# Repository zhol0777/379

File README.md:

# 379

this is a pcb replacement for the noxary 378. pinout isn't the same.

pcb edge cuts were provided by islandworks studio.

thanks to invis and chippy for providing plate file, xondat discord is shut down so you can't get in no more.

thanks to xyz for simple stm boot circuit.

untested. good luck.

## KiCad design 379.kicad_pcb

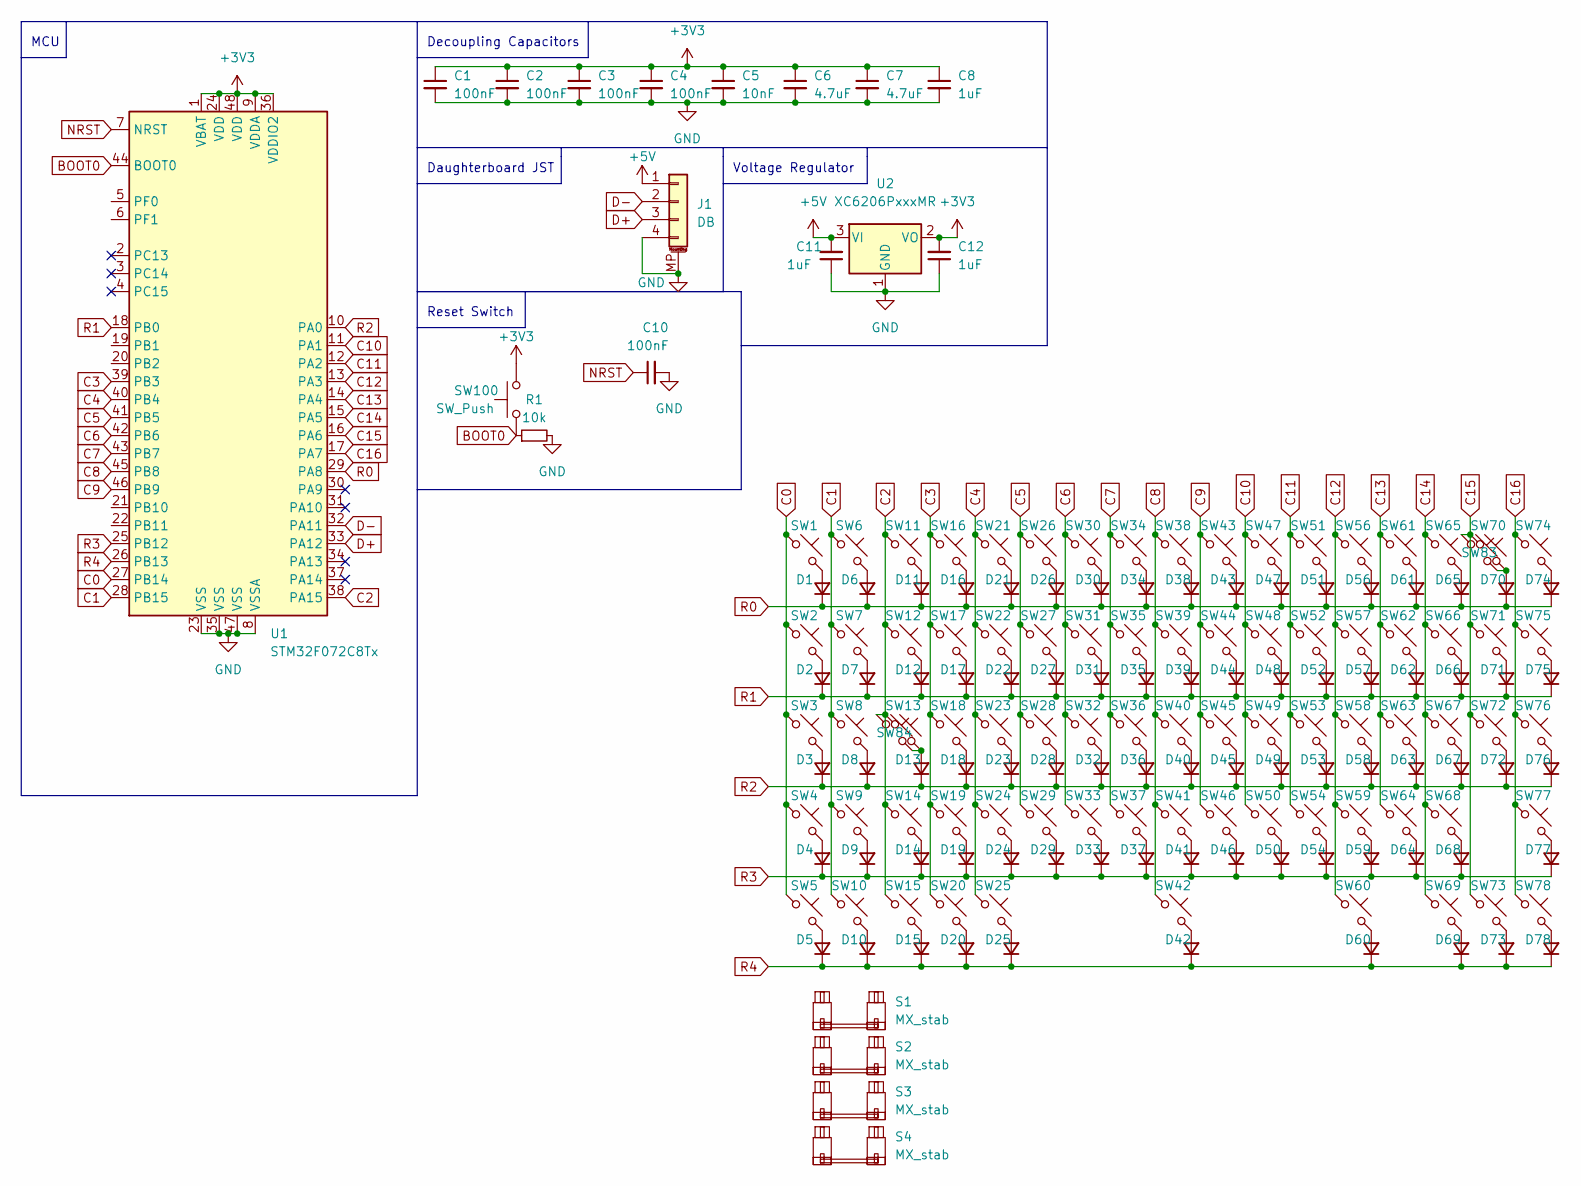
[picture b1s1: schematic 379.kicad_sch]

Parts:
C1, C2, C3, C4, C10: 100nF; C_0402_1005Metric
C5: 10nF; C_0402_1005Metric
C6, C7: 4.7uF; C_0402_1005Metric
C8, C11, C12: 1uF; C_0402_1005Metric
D1, D2, D3, D4, D5, D6, D7, D8, D9, D10, D11, D12, D13, D14, D15, D16, D17, D18, D19, D20, D21, D22, D23, D24, D25, D26, D27, D28, D29, D30, D31, D32, D33, D34, D35, D36, D37, D38, D39, D40, D41, D42, D43, D44, D45, D46, D47, D48, D49, D50, D51, D52, D53, D54, D56, D57, D58, D59, D60, D61, D62, D63, D64, D65, D66, D67, D68, D69, D70, D71, D72, D73, D74, D75, D76, D77, D78: D_Small; D_SOD-123
J1: DB; JST_SH_SM04B-SRSS-TB_1x04-1MP_P1.00mm_Horizontal
R1: 10k; R_0603_1608Metric
S1: MX_stab; STAB_MX_P_2u
S2, S3: MX_stab; STAB_MX_2.25u
S4: MX_stab; STAB_MX_7u
SW1, SW2, SW3, SW4, SW5, SW6, SW7, SW8, SW9, SW10, SW11, SW14, SW16, SW17, SW18, SW19, SW20, SW21, SW22, SW23, SW24, SW26, SW27, SW28, SW29, SW30, SW31, SW32, SW33, SW34, SW35, SW36, SW37, SW38, SW39, SW40, SW41, SW42, SW43, SW44, SW45, SW46, SW47, SW48, SW49, SW50, SW51, SW52, SW53, SW54, SW56, SW57, SW58, SW59, SW61, SW62, SW63, SW64, SW65, SW66, SW67, SW68, SW69, SW70, SW71, SW72, SW73, SW74, SW75, SW76, SW77, SW78, SW83: MX_SW_solder; SW_MX_1u
SW12, SW15, SW25, SW60: MX_SW_solder; SW_MX_1.5u
SW13: MX_SW_solder; SW_MX_1.75u
SW84: MX_SW_solder; SW_MX_1.75u_STP_1.25
SW100: SW_Push; PinHeader_1x02_P2.00mm_Vertical
U1: STM32F072C8Tx; LQFP-48_7x7mm_P0.5mm
U2: XC6206PxxxMR; SOT-23

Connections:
+3V3: C1.1, C2.1, C3.1, C4.1, C5.1, C6.1, C7.1, C8.1, C12.2, SW100.2, U1.1 (VBAT), U1.9 (VDDA), U1.24 (VDD), U1.36 (VDDIO2), U1.48 (VDD), U2.2 (VO)
+5V: C11.2, J1.1, U2.3 (VI)
BOOT0: R1.1, SW100.1, U1.44 (BOOT0)
C0: SW1.1, SW2.1, SW3.1, SW4.1, SW5.1, U1.27 (PB14)
C1: SW6.1, SW7.1, SW8.1, SW9.1, SW10.1, U1.28 (PB15)
C2: SW11.1, SW12.1, SW13.1, SW14.1, SW15.1, SW84.1, U1.38 (PA15)
C3: SW16.1, SW17.1, SW18.1, SW19.1, SW20.1, U1.39 (PB3)
C4: SW21.1, SW22.1, SW23.1, SW24.1, SW25.1, U1.40 (PB4)
C5: SW26.1, SW27.1, SW28.1, SW29.1, U1.41 (PB5)
C6: SW30.1, SW31.1, SW32.1, SW33.1, U1.42 (PB6)
C7: SW34.1, SW35.1, SW36.1, SW37.1, U1.43 (PB7)
C8: SW38.1, SW39.1, SW40.1, SW41.1, SW42.1, U1.45 (PB8)
C9: SW43.1, SW44.1, SW45.1, SW46.1, U1.46 (PB9)
C10: SW47.1, SW48.1, SW49.1, SW50.1, U1.11 (PA1)
C11: SW51.1, SW52.1, SW53.1, SW54.1, U1.12 (PA2)
C12: SW56.1, SW57.1, SW58.1, SW59.1, SW60.1, U1.13 (PA3)
C13: SW61.1, SW62.1, SW63.1, SW64.1, U1.14 (PA4)
C14: SW65.1, SW66.1, SW67.1, SW68.1, SW69.1, U1.15 (PA5)
C15: SW70.1, SW71.1, SW72.1, SW73.1, SW83.1, U1.16 (PA6)
C16: SW74.1, SW75.1, SW76.1, SW77.1, SW78.1, U1.17 (PA7)
D+: J1.3, U1.33 (PA12)
D-: J1.2, U1.32 (PA11)
GND: C1.2, C2.2, C3.2, C4.2, C5.2, C6.2, C7.2, C8.2, C10.2, C11.1, C12.1, J1.4, J1.MP (MountPin), R1.2, U1.8 (VSSA), U1.23 (VSS), U1.35 (VSS), U1.47 (VSS), U2.1 (GND)
NRST: C10.1, U1.7 (NRST)
unnamed: D1.2 (A), SW1.2
unnamed: D2.2 (A), SW2.2
unnamed: D3.2 (A), SW3.2
unnamed: D4.2 (A), SW4.2
unnamed: D5.2 (A), SW5.2
unnamed: D6.2 (A), SW6.2
unnamed: D7.2 (A), SW7.2
unnamed: D8.2 (A), SW8.2
unnamed: D9.2 (A), SW9.2
unnamed: D10.2 (A), SW10.2
unnamed: D11.2 (A), SW11.2
unnamed: D12.2 (A), SW12.2
unnamed: D13.2 (A), SW13.2, SW84.2
unnamed: D14.2 (A), SW14.2
unnamed: D15.2 (A), SW15.2
unnamed: D16.2 (A), SW16.2
unnamed: D17.2 (A), SW17.2
unnamed: D18.2 (A), SW18.2
unnamed: D19.2 (A), SW19.2
unnamed: D20.2 (A), SW20.2
unnamed: D21.2 (A), SW21.2
unnamed: D22.2 (A), SW22.2
unnamed: D23.2 (A), SW23.2
unnamed: D24.2 (A), SW24.2
unnamed: D25.2 (A), SW25.2
unnamed: D26.2 (A), SW26.2
unnamed: D27.2 (A), SW27.2
unnamed: D28.2 (A), SW28.2
unnamed: D29.2 (A), SW29.2
unnamed: D30.2 (A), SW30.2
unnamed: D31.2 (A), SW31.2
unnamed: D32.2 (A), SW32.2
unnamed: D33.2 (A), SW33.2
unnamed: D34.2 (A), SW34.2
unnamed: D35.2 (A), SW35.2
unnamed: D36.2 (A), SW36.2
unnamed: D37.2 (A), SW37.2
unnamed: D38.2 (A), SW38.2
unnamed: D39.2 (A), SW39.2
unnamed: D40.2 (A), SW40.2
unnamed: D41.2 (A), SW41.2
unnamed: D42.2 (A), SW42.2
unnamed: D43.2 (A), SW43.2
unnamed: D44.2 (A), SW44.2
unnamed: D45.2 (A), SW45.2
unnamed: D46.2 (A), SW46.2
unnamed: D47.2 (A), SW47.2
unnamed: D48.2 (A), SW48.2
unnamed: D49.2 (A), SW49.2
unnamed: D50.2 (A), SW50.2
unnamed: D51.2 (A), SW51.2
unnamed: D52.2 (A), SW52.2
unnamed: D53.2 (A), SW53.2
unnamed: D54.2 (A), SW54.2
unnamed: D56.2 (A), SW56.2
unnamed: D57.2 (A), SW57.2
unnamed: D58.2 (A), SW58.2
unnamed: D59.2 (A), SW59.2
unnamed: D60.2 (A), SW60.2
unnamed: D61.2 (A), SW61.2
unnamed: D62.2 (A), SW62.2
unnamed: D63.2 (A), SW63.2
unnamed: D64.2 (A), SW64.2
unnamed: D65.2 (A), SW65.2
unnamed: D66.2 (A), SW66.2
unnamed: D67.2 (A), SW67.2
unnamed: D68.2 (A), SW68.2
unnamed: D69.2 (A), SW69.2
unnamed: D70.2 (A), SW70.2, SW83.2
unnamed: D71.2 (A), SW71.2
unnamed: D72.2 (A), SW72.2
unnamed: D73.2 (A), SW73.2
unnamed: D74.2 (A), SW74.2
unnamed: D75.2 (A), SW75.2
unnamed: D76.2 (A), SW76.2
unnamed: D77.2 (A), SW77.2
unnamed: D78.2 (A), SW78.2
R0: D1.1 (K), D6.1 (K), D11.1 (K), D16.1 (K), D21.1 (K), D26.1 (K), D30.1 (K), D34.1 (K), D38.1 (K), D43.1 (K), D47.1 (K), D51.1 (K), D56.1 (K), D61.1 (K), D65.1 (K), D70.1 (K), D74.1 (K), U1.29 (PA8)
R1: D2.1 (K), D7.1 (K), D12.1 (K), D17.1 (K), D22.1 (K), D27.1 (K), D31.1 (K), D35.1 (K), D39.1 (K), D44.1 (K), D48.1 (K), D52.1 (K), D57.1 (K), D62.1 (K), D66.1 (K), D71.1 (K), D75.1 (K), U1.18 (PB0)
R2: D3.1 (K), D8.1 (K), D13.1 (K), D18.1 (K), D23.1 (K), D28.1 (K), D32.1 (K), D36.1 (K), D40.1 (K), D45.1 (K), D49.1 (K), D53.1 (K), D58.1 (K), D63.1 (K), D67.1 (K), D72.1 (K), D76.1 (K), U1.10 (PA0)
R3: D4.1 (K), D9.1 (K), D14.1 (K), D19.1 (K), D24.1 (K), D29.1 (K), D33.1 (K), D37.1 (K), D41.1 (K), D46.1 (K), D50.1 (K), D54.1 (K), D59.1 (K), D64.1 (K), D68.1 (K), D77.1 (K), U1.25 (PB12)
R4: D5.1 (K), D10.1 (K), D15.1 (K), D20.1 (K), D25.1 (K), D42.1 (K), D60.1 (K), D69.1 (K), D73.1 (K), D78.1 (K), U1.26 (PB13)

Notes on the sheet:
Voltage Regulator
Reset Switch
MCU
Daughterboard JST
Decoupling Capacitors

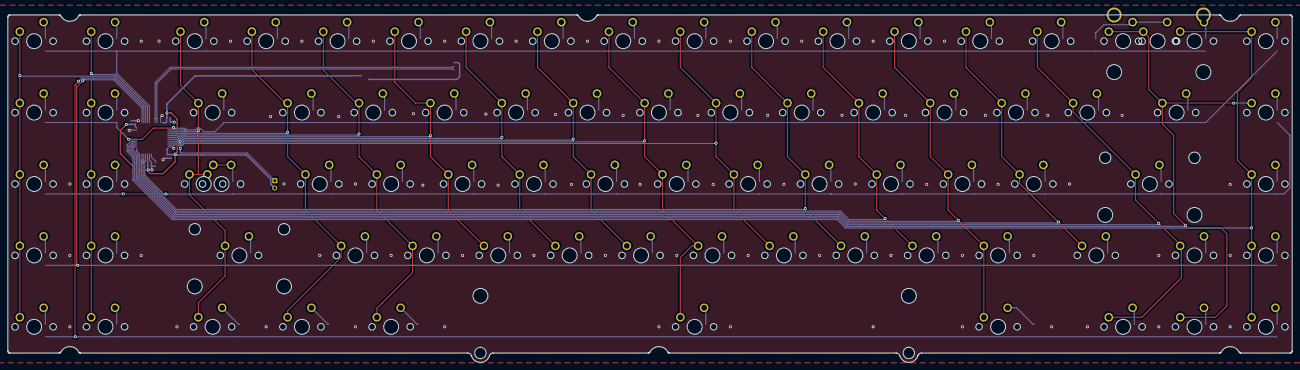
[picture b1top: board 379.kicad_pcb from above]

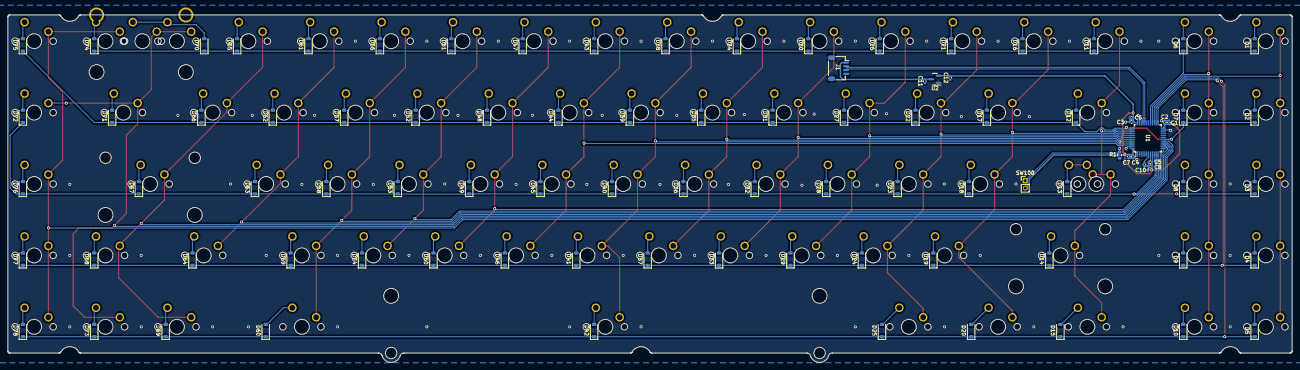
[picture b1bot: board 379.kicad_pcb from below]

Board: 2 copper layers, 342.6 x 92.7 mm, 176 parts (93 on the bottom side), 106 nets.

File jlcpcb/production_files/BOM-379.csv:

Comment,Designator,Footprint,LCSC
10nF,C5,C_0402_1005Metric,C15195
100nF,"C1,C10,C2,C3,C4",C_0402_1005Metric,C1525
4.7uF,"C6,C7",C_0402_1005Metric,C23733
10k,R1,R_0603_1608Metric,C25804
DB,J1,JST_SH_SM04B-SRSS-TB_1x04-1MP_P1.00mm_Horizontal,C2845363
1uF,"C11,C12,C8",C_0402_1005Metric,C52923
XC6206PxxxMR,U2,SOT-23,C5446
STM32F072C8Tx,U1,LQFP-48_7x7mm_P0.5mm,C80488
D_Small,"D1,D10,D11,D12,D13,D14,D15,D16,D17,D18,D19,D2,D20,D21,D22,D23,D24,D25,D26,D27,D28,D29,D3,D30,D31,D32,D33,D34,D35,D36,D37,D38,D39,D4,D40,D41,D42,D43,D44,D45,D46,D47,D48,D49,D5,D50,D51,D52,D53,D54,D56,D57,D58,D59,D6,D60,D61,D62,D63,D64,D65,D66,D67,D68,D69,D7,D70,D71,D72,D73,D74,D75,D76,D77,D78,D8,D9",D_SOD-123,C8598

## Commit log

2024-01-29 init
2024-08-04 this bad boy is hot to go
